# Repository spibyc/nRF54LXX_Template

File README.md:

# nRF54LXX Hardware Template (QFN-48)

Reusable KiCad schematic and PCB layout template for designs based on the Nordic Semiconductor **nRF54L15 / nRF54L10 / nRF54L05** family.

The purpose of this repository is to provide a known starting point for new nRF54L designs rather than recreating the MCU support circuitry, RF section, programming interface, and component selection for every project.

For a new design, copy this template and build the application-specific circuitry around it.

## Overview

The template currently uses the **nRF54L15-QFAA-R7** as the populated MCU and includes the core circuitry required around the device.

The PCB is already laid out so that the placement and routing of the critical MCU, clock, power, and RF components can be reused between projects.

Included in the template:

- nRF54L15-QFAA-R7 MCU
- 32 MHz high-frequency crystal and associated components
- 32.768 kHz low-frequency crystal
- MCU supply decoupling
- Internal 0.9V regulator components
- RF matching network
- BLE RF routing
- Murata MM8130-2600RA2 RF connector
- SWD programming/debug interface
- Tag-Connect TC2050 programming footprint
- MCU reset connection
- Populated BOM for the template components

## Repository Contents

```text
nRF54LXX.kicad_sch    KiCad template schematic
nRF54LXX.kicad_pcb    KiCad PCB layout
BOM.csv               Template bill of materials
README.md             Project documentation
```

## Intended Use

This project is intended to act as a **master template** for future nRF54L-based hardware.

When starting a new product:

1. Copy the schematic and PCB files into the new project.
2. Rename the KiCad project as required.
3. Retain the MCU support, RF, clock, power, and programming sections.
4. Add the application-specific peripherals, power supplies, sensors, drivers, connectors, etc.
5. Route the new circuitry around the existing nRF54L layout.
6. Review the final design against the requirements of the exact nRF54L device being fitted.

The main advantage of this approach is that the sensitive RF and MCU support circuitry does not need to be recreated from scratch for every design.

## RF / BLE Section

The template includes the RF circuitry and PCB layout for the Bluetooth Low Energy interface.

The populated RF network includes:

| Reference | Value |
|---|---:|
| L2 | 2.7 nH |
| L3 | 3.5 nH |
| L4 | 3.5 nH |
| C9 | 3.9 pF |
| C10 | 1.5 pF |
| C11 | 2 pF |
| C12 | 0.3 pF |
| C13 | 1.4 pF |
| R1 | 0 Ω |

A **Murata MM8130-2600RA2** RF connector is included as J1.

The RF component placement and routing in the PCB file should be treated as a critical part of the template. Avoid moving RF components or changing RF trace geometry unless the RF design is being deliberately re-evaluated.

> **Important:** Copying this layout does not remove the need for RF verification on the final product. Changes to the PCB stack-up, ground structure, enclosure, antenna, nearby components, or mechanical construction can affect RF performance.

## Clocking

Two external crystals are included.

### 32 MHz HF Crystal

**Y2 — 32 MHz, 2016 4-pin package**

The 32 MHz crystal and its surrounding components are positioned close to the MCU to minimise trace length and interference.

### 32.768 kHz LF Crystal

**Y1 — 32.768 kHz, 2012 2-pin package**

The low-frequency crystal is provided for applications requiring the external 32.768 kHz clock source.

If the LF crystal is not required by a particular application, its use should be reviewed against the firmware configuration and Nordic documentation before removing it.

## Programming and Debug

The template includes the connections required for SWD programming and debugging.

Signals provided include:

- `SWDIO`
- `SWDCLK`
- `MCU_RST`
- Power/reference connections required by the programming interface

J2 uses a **Tag-Connect TC2050** style footprint, allowing production programming and development access without fitting a permanent header to the finished PCB.

This section is intended to remain in derived designs so that new boards have a consistent programming interface.

## Internal regulator and Decoupling

The template includes the local supply filtering, decoupling, and internal 0.9V regulator support components used around the MCU.

Current BOM values include:

| Reference | Value |
|---|---:|
| C1 | 10 µF |
| C2–C5 | 100 nF |
| C6 | 10 nF |
| C7–C8 | 2.2 µF |
| L1 | 4.7 µH |
| FB1 | 120 Ω / 0.2 A ferrite bead |

These components are already placed around the MCU in the PCB layout.

Their placement is intentional. In derived projects, avoid moving decoupling and power components away from the MCU simply to make application routing easier.

## MCU

The current template is populated with:

**Nordic Semiconductor nRF54L15-QFAA-R7**

The template is intended for use across compatible members of the nRF54L family, including:

- nRF54L15
- nRF54L10
- nRF54L05

When changing MCU variant, verify pin compatibility, available peripherals, memory configuration, package requirements, power configuration, and firmware target before manufacturing the board.

Do not assume that every nRF54L variant is electrically interchangeable without checking the relevant Nordic documentation.

## Bill of Materials

`BOM.csv` contains the components currently used by the template, including their references, quantities, values, and PCB footprints.

The current template contains the following major parts:

| Component | Description |
|---|---|
| IC1 | nRF54L15-QFAA-R7 |
| J1 | Murata MM8130-2600RA2 RF connector |
| J2 | Tag-Connect TC2050 programming interface |
| Y1 | 32.768 kHz crystal |
| Y2 | 32 MHz crystal |
| L1 | 4.7 µH power inductor |
| FB1 | 120 Ω / 0.2 A ferrite bead |
| L2–L4 | RF inductors |
| C1–C13 | Power, clock and RF capacitors |
| R1 | 0 Ω RF component |

The BOM should be copied into each derived project and updated as application-specific components are added.

## PCB Layout Guidance

Several parts of this layout should be considered **template-controlled / critical circuitry**.

In particular, avoid unnecessary modification of:

- MCU decoupling placement
- MCU power components
- 32 MHz crystal placement and routing
- RF matching network placement
- RF routing
- RF ground structure
- SWD programming connections

Application circuitry can then be added around this core layout.

If the board stack-up or RF implementation changes substantially, the RF section should be reviewed rather than assumed to remain valid.

## Design Philosophy

The goal of this repository is simple:

> **Do the critical nRF54L implementation once, then reuse it.**

A new product should not require rebuilding the MCU support circuitry from a blank schematic.

Instead, this repository provides a common starting point containing the circuitry that is likely to remain largely unchanged between designs:

```text
                 ┌─────────────────────────┐
                 │       nRF54LXX MCU      │
                 │                         │
                 │   Power / Decoupling    │
                 │   HF/LF Clocking        │
                 │   SWD Programming       │
                 │   BLE RF Interface      │
                 └────────────┬────────────┘
                              │
                         Application
                           Circuitry
```

This reduces repeated design work and helps maintain consistency between nRF54L-based products.

## Important Notes

This repository is a **design template**, not a substitute for final design verification.

Before releasing a derived PCB for manufacture:

- Verify the exact MCU variant being used.
- Review the latest Nordic reference circuitry and documentation.
- Run KiCad ERC and DRC.
- Verify all footprints against the selected manufacturer part numbers.
- Confirm the PCB stack-up.
- Review controlled/critical RF geometry.
- Verify power integrity and decoupling.
- Verify SWD programming on assembled hardware.
- Verify both clock sources where used.
- Perform RF testing on the final assembled product.
- Update the BOM for the final product.

Any changes to the RF path, matching components, antenna implementation, PCB stack-up, or surrounding mechanical design should be treated as potentially affecting RF performance.

## Status

This repository is intended to evolve as the nRF54L implementation is validated and reused in future designs.

Improvements to the common MCU circuitry should be made to the master template so that future projects inherit the latest validated implementation.

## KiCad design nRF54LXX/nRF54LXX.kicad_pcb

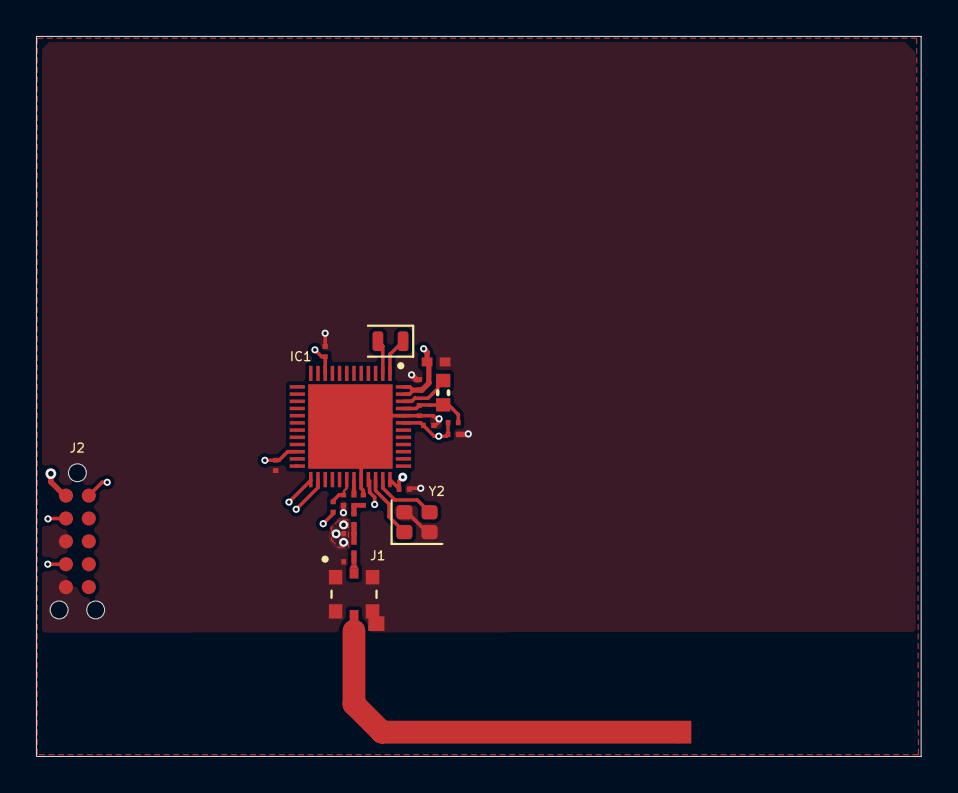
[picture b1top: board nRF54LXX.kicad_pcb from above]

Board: 4 copper layers, 49.1 x 40.0 mm, 24 parts (0 on the bottom side), 18 nets.

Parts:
C1: 10u; CAPC1005X04L
C2, C3, C4, C5: 100n; CAPC0603X03L_C
C6: 10n; CAPC0603X03L_C
C7, C8: 2.2u; CAPC0603X03L_C
C9: 3.9p; CAPC0603X03L_C
C10: 1.5p; CAPC0603X03L_C
C11: 2p; CAPC0603X03L_C
C12: 0.3p; CAPC0603X03L_C
C13: 1.4p; CAPC0603X03L_C
FB1: 120R/0.2A; INDC0603X03L_C
IC1: NRF54L15-QFAA-R7; QFN40P600X600X90-49N-D
J1: MM8130-2600RA2; MURATA_MM8130-2600RA2
J2: Programmer; TC2050-IDC-NL-050-ALL
L1: 4.7u; INDC1608X06L
L2: 2.7n; INDC0603X03L_C
L3, L4: 3.5n; INDC0603X03L_C
R1: 0; RESC0603X03L_C
Y1: 32.768kHz; Crystal_SMD_2012-2Pin_2.0x1.2mm
Y2: 32MHz; Crystal_SMD_2016-4Pin_2.0x1.6mm

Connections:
+3V3: C1.1, C2.1, C3.1, C4.1, C5.1, IC1.10 (VDD_1), IC1.22 (VDD_2), IC1.36 (VDD_3), IC1.47 (VDD_4), IC1.48 (VDD_5), J2.1
/ANT: C13.1, J1.2 (OUT)
/MCU_RST: J2.10, R1.2
/SWDCLK: IC1.26 (SWDCLK), J2.4
/SWDIO: IC1.25 (SWDIO), J2.2
GND: C1.2, C2.2, C3.2, C4.2, C5.2, C6.2, C7.2, C8.2, C9.2, C10.2, C11.2, C12.2, C13.2, IC1.32 (VSS_PA), IC1.44 (VSS), IC1.49 (EP), J1.G (GND), J2.3, J2.5, Y2.2 (GND), Y2.4 (GND)
unnamed: C10.1, L2.1, L3.2
unnamed: C11.1, L3.1, L4.2
unnamed: IC1.31 (ANT), L2.2
unnamed: IC1.46 (DCC), L1.1
unnamed: C6.1, C7.1, FB1.1, IC1.33 (DECRF), IC1.43 (DECA)
unnamed: C8.1, FB1.2, IC1.45 (DECD), L1.2
unnamed: C9.1, IC1.30 (NRESET), R1.1
unnamed: IC1.34 (XC1), Y2.1
unnamed: IC1.35 (XC2), Y2.3
unnamed: IC1.1 (P1.00/XL1), Y1.1
unnamed: IC1.2 (P1.01/XL2), Y1.2
unnamed: C12.1, J1.1 (IN), L4.1

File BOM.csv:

Reference,Qty,Value,Footprint
C1,1,10uF,0402_1005Metric
"C2,C3,C4,C5",4,100nF,0201_0603Metric
C6,1,10nF,0201_0603Metric
"C7,C8",2,2.2uF,0201_0603Metric
C9,1,3.9pF,0201_0603Metric
C10,1,1.5pF,0201_0603Metric
C11,1,2pF,0201_0603Metric
C12,1,0.3pF,0201_0603Metric
C13,1,1.4pF,0201_0603Metric
FB1,1,120R/0.2A,0201_0603Metric
IC1,1,NRF54L15-QFAA-R7,QFN48
J1,1,MM8130-2600RA2,MM8130-2600RA2
L1,1,4.7uH,0603_1608Metric
L2,1,2.7nH,0201_0603Metric
"L3,L4",2,3.5nH,0201_0603Metric
R1,1,0Ω,0201_0603Metric
Y1,1,32.768kHz,2012-2Pin_2.0x1.2mm
Y2,1,32MHz,2016-4Pin_2.0x1.6mm
